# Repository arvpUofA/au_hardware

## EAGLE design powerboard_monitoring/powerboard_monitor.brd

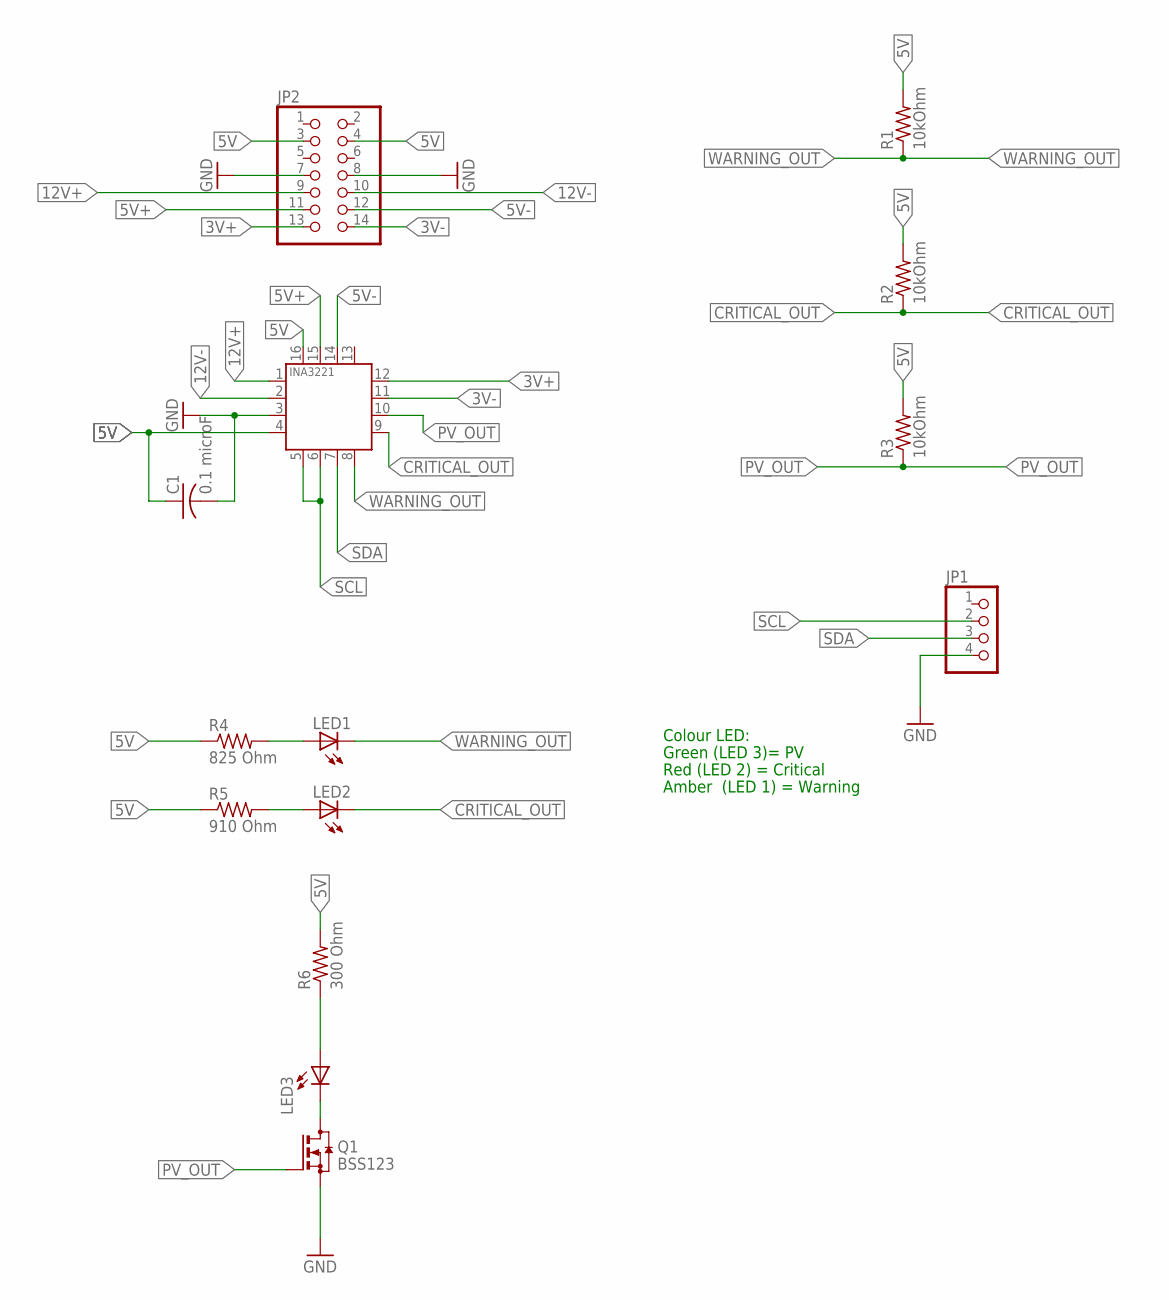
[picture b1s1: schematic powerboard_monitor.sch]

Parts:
C1: 0.1 microF; C1206
JP1: PINHD-1X4; 1X04
JP2: PINHD-2X7; 2X07
LED1, LED2, LED3: LEDSMT1206; 1206
Q1: BSS123; SOT23
R1, R2, R3: 10kOhm; R1206
R4: 825 Ohm; R1206
R5: 910 Ohm; R1206
R6: 300 Ohm; R1206
U1: INA3221.; HVQFN16_4X4

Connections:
3V+: JP2.13, U1.12 (IN+1)
3V-: JP2.14, U1.11 (IN-1)
5V: C1.1, JP2.3, JP2.4, R1.2, R2.2, R3.2, R4.1, R5.1, R6.2, U1.4 (VS), U1.16 (VPU)
5V+: JP2.11, U1.15 (IN+2)
5V-: JP2.12, U1.14 (IN-2)
12V+: JP2.9, U1.1 (IN-3)
12V-: JP2.10, U1.2 (IN+3)
CRITICAL_OUT: LED2.C, R2.1, U1.9 (CRITICAL)
GND: C1.2, JP1.4, JP2.7, JP2.8, Q1.2 (S), U1.3 (GND); also elsewhere on the board
unnamed: LED3.A, R6.1
unnamed: LED3.C, Q1.3 (D)
unnamed: LED1.A, R4.2
unnamed: LED2.A, R5.2
PV_OUT: Q1.1 (G), R3.1, U1.10 (PV)
SCL: JP1.2, U1.5 (A0), U1.6 (SCL); also elsewhere on the board
SDA: JP1.3, U1.7 (SDA); also elsewhere on the board
WARNING_OUT: LED1.C, R1.1, U1.8 (WARNING)

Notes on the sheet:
Colour LED:
Green (LED 3)= PV
Red (LED 2) = Critical
Amber (LED 1) = Warning

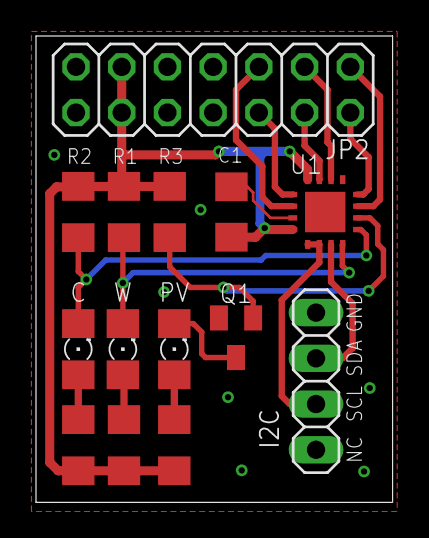
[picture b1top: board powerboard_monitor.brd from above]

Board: 2 copper layers, 19.8 x 25.9 mm, 16 parts (0 on the bottom side), 17 nets.

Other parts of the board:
I2C: 1X04
U$1: LETTER_P
U$2: DOCFIELD

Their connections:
GND: I2C.4; also elsewhere on the board
SCL: I2C.2; also elsewhere on the board
SDA: I2C.3; also elsewhere on the board

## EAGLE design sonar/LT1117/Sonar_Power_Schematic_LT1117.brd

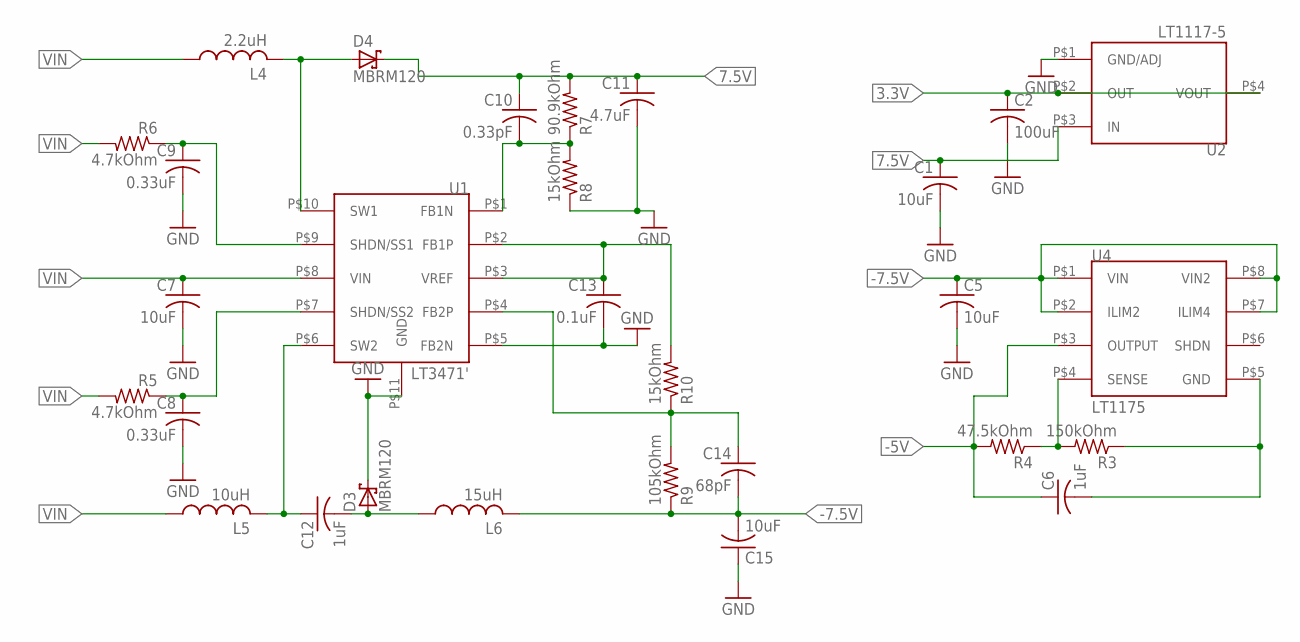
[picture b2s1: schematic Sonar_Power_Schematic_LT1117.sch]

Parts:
C1, C5, C7, C15: 10uF; C0603
C2: 100uF; C1210
C6, C12: 1uF; C0603
C8, C9: 0.33uF; C0603
C10: 0.33pF; C0603
C11: 4.7uF; C0603
C13: 0.1uF; C0603
C14: 68pF; C0603
D3, D4: MBRM120; DO-216AA
L4: 2.2uH; NS4.9X4.9
L5: 10uH; NS5X5
L6: 15uH; NS5X5
R3: 150kOhm; R0603
R4: 47.5kOhm; R0603
R5, R6: 4.7kOhm; R0603
R7: 90.9kOhm; R0603
R8, R10: 15kOhm; R0603
R9: 105kOhm; R0603
U1: LT3471'; 10-WFDFN
U2: LT1117-5; SOT233-3
U4: LT1175; 8-SOIC

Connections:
3.3V: C2.1, U2.P$2 (OUT), U2.P$4 (VOUT)
7.5V: C1.1, C10.1, C11.1, D4.P$1 (C), R7.2, U2.P$3 (IN)
-5V: C6.1, R4.2, U4.P$3 (OUTPUT)
-7.5V: C5.1, C14.2, C15.2, L6.P$2 (2), R9.1, U4.P$1 (VIN), U4.P$2 (ILIM2), U4.P$7 (ILIM4), U4.P$8 (VIN2)
GND: C1.2, C2.2, C5.2, C7.2, C8.2, C9.2, C11.2, C13.2, C15.1, D3.P$1 (C), R8.1, U1.P$5 (FB2N), U1.P$11 (GND), U2.P$1 (GND/ADJ)
unnamed: R3.2, R4.1, U4.P$4 (SENSE)
unnamed: C6.2, R3.1, U4.P$5 (GND)
unnamed: D4.P$2 (A), L4.P$2 (2), U1.P$10 (SW1)
unnamed: C10.2, R7.1, R8.2, U1.P$1 (FB1N)
unnamed: C12.1, L5.P$2 (2), U1.P$6 (SW2)
unnamed: C12.2, D3.P$2 (A), L6.P$1 (1)
unnamed: C14.1, R9.2, R10.1, U1.P$4 (FB2P)
SS1: C9.1, R6.1, U1.P$9 (SHDN/SS1)
SS2: C8.1, R5.1, U1.P$7 (SHDN/SS2)
VIN: C7.1, L4.P$1 (1), L5.P$1 (1), R5.2, R6.2, U1.P$8 (VIN)
VREF: C13.1, R10.2, U1.P$2 (FB1P), U1.P$3 (VREF)

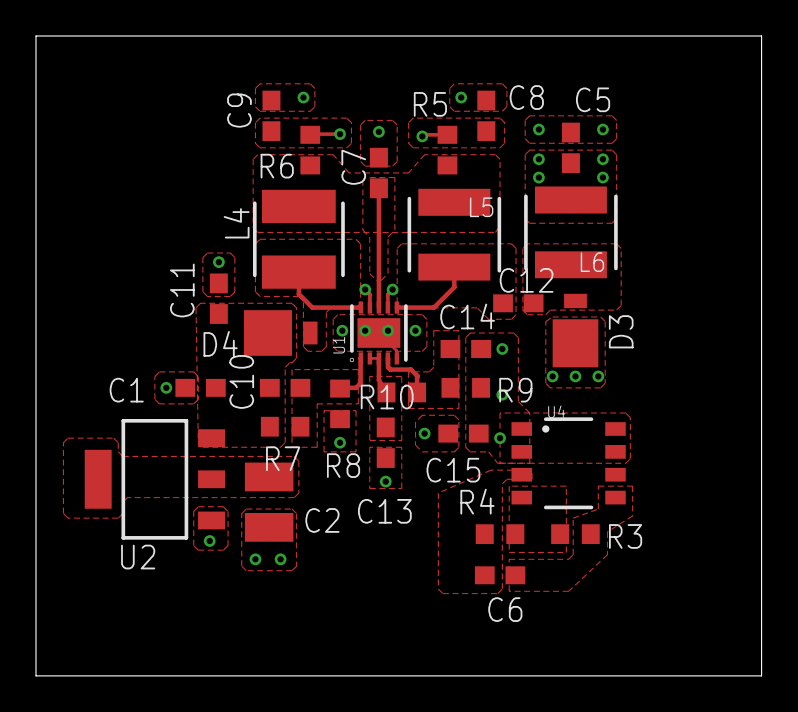
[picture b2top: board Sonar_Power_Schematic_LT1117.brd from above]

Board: 4 copper layers, 40.3 x 35.5 mm, 29 parts (0 on the bottom side), 16 nets.

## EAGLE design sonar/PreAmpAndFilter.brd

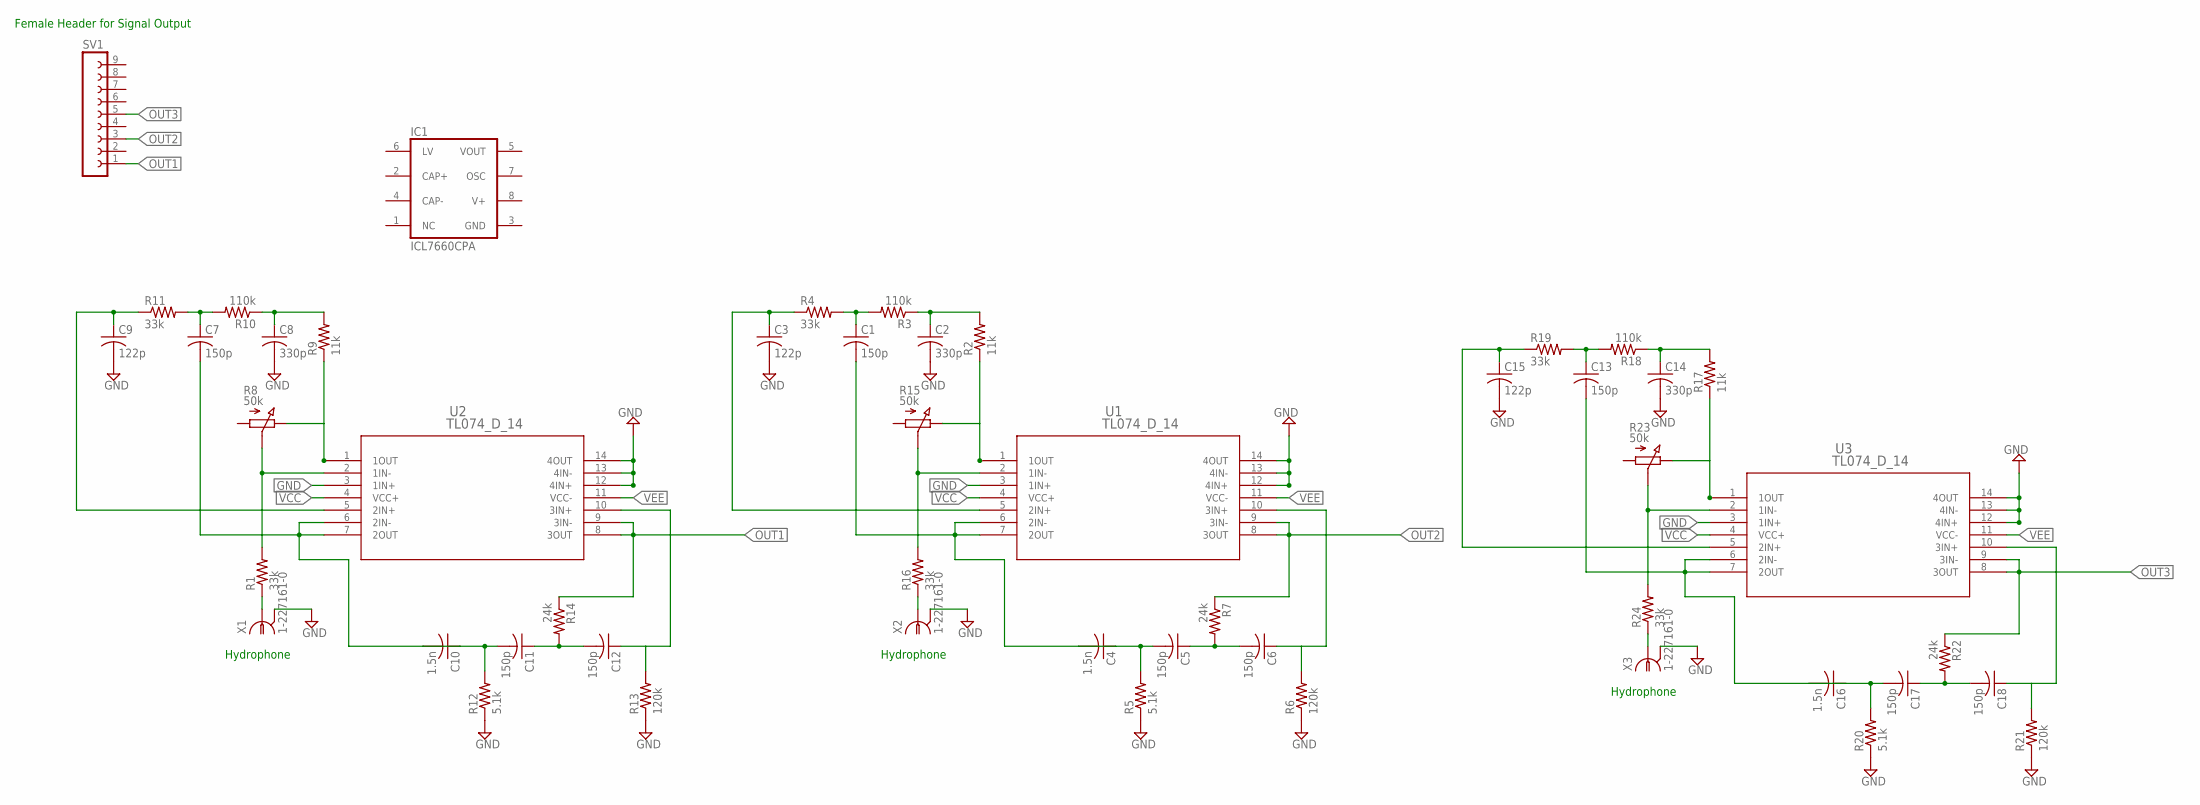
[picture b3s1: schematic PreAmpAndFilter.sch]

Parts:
C1, C5, C6, C7, C11, C12, C13, C17, C18: 150p; C025-024X044
C2, C8, C14: 330p; C025-024X044
C3, C9, C15: 122p; C025-024X044
C4, C10, C16: 1.5n; C025-024X044
IC1: ICL7660CPA; DIL08
R1, R4, R11, R16, R19, R24: 33k; 0204V
R2, R9, R17: 11k; 0204V
R3, R10, R18: 110k; 0204V
R5, R12, R20: 5.1k; 0204V
R6, R13, R21: 120k; 0204V
R7, R14, R22: 24k; 0204V
R8, R15, R23: 50k; PC25
SV1: FE09-1; FE09
U1, U2, U3: TL074_D_14; D14
X1, X2, X3: 1-227161-0; AMP_227161

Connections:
GND: C2.2, C3.2, C8.2, C9.2, C14.2, C15.2, IC1.3 (GND), R1.2, R5.1, R6.1, R8.S, R12.1, R13.1, R15.S, R16.2, R20.1, R21.1, R23.S, R24.2, U1.2 (1IN-), U1.3 (1IN+), U1.12 (4IN+), U1.13 (4IN-), U1.14 (4OUT), U2.2 (1IN-), U2.3 (1IN+), U2.12 (4IN+), U2.13 (4IN-), U2.14 (4OUT), U3.2 (1IN-), U3.3 (1IN+), U3.12 (4IN+), U3.13 (4IN-), U3.14 (4OUT), X1.2, X2.2, X3.2
unnamed: R1.1, X1.1
unnamed: R2.1, R15.E, U1.1 (1OUT)
unnamed: C2.1, R2.2, R3.1
unnamed: C1.1, R3.2, R4.2
unnamed: C1.2, C4.1, C4.2, C5.2, R5.2, U1.6 (2IN-), U1.7 (2OUT)
unnamed: C5.1, C6.2, R7.2
unnamed: R8.E, R9.1, U2.1 (1OUT)
unnamed: C8.1, R9.2, R10.1
unnamed: C7.1, R10.2, R11.2
unnamed: C7.2, C10.1, C10.2, C11.2, R12.2, U2.6 (2IN-), U2.7 (2OUT)
unnamed: C11.1, C12.2, R14.2
unnamed: R16.1, X2.1
unnamed: R17.1, R23.E, U3.1 (1OUT)
unnamed: C14.1, R17.2, R18.1
unnamed: C13.1, R18.2, R19.2
unnamed: C13.2, C16.1, C16.2, C17.2, R20.2, U3.6 (2IN-), U3.7 (2OUT)
unnamed: C17.1, C18.2, R22.2
unnamed: R24.1, X3.1
OUT1: R14.1, SV1.1, U2.8 (3OUT), U2.9 (3IN-)
OUT2: R7.1, SV1.3, U1.8 (3OUT), U1.9 (3IN-)
OUT3: R22.1, SV1.5, U3.8 (3OUT), U3.9 (3IN-)
V+: IC1.8 (V+)
VCC: U1.4 (VCC+), U2.4 (VCC+), U3.4 (VCC+)
VCC+: C9.1, R11.1, U2.5 (2IN+)
VCC+1: C3.1, R4.1, U1.5 (2IN+)
VCC+2: C15.1, R19.1, U3.5 (2IN+)
VCC-: C12.1, R13.2, U2.10 (3IN+)
VCC-1: C6.1, R6.2, U1.10 (3IN+)
VCC-2: C18.1, R21.2, U3.10 (3IN+)
VEE: U1.11 (VCC-), U2.11 (VCC-), U3.11 (VCC-)

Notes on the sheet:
Female Header for Signal Output
Hydrophone

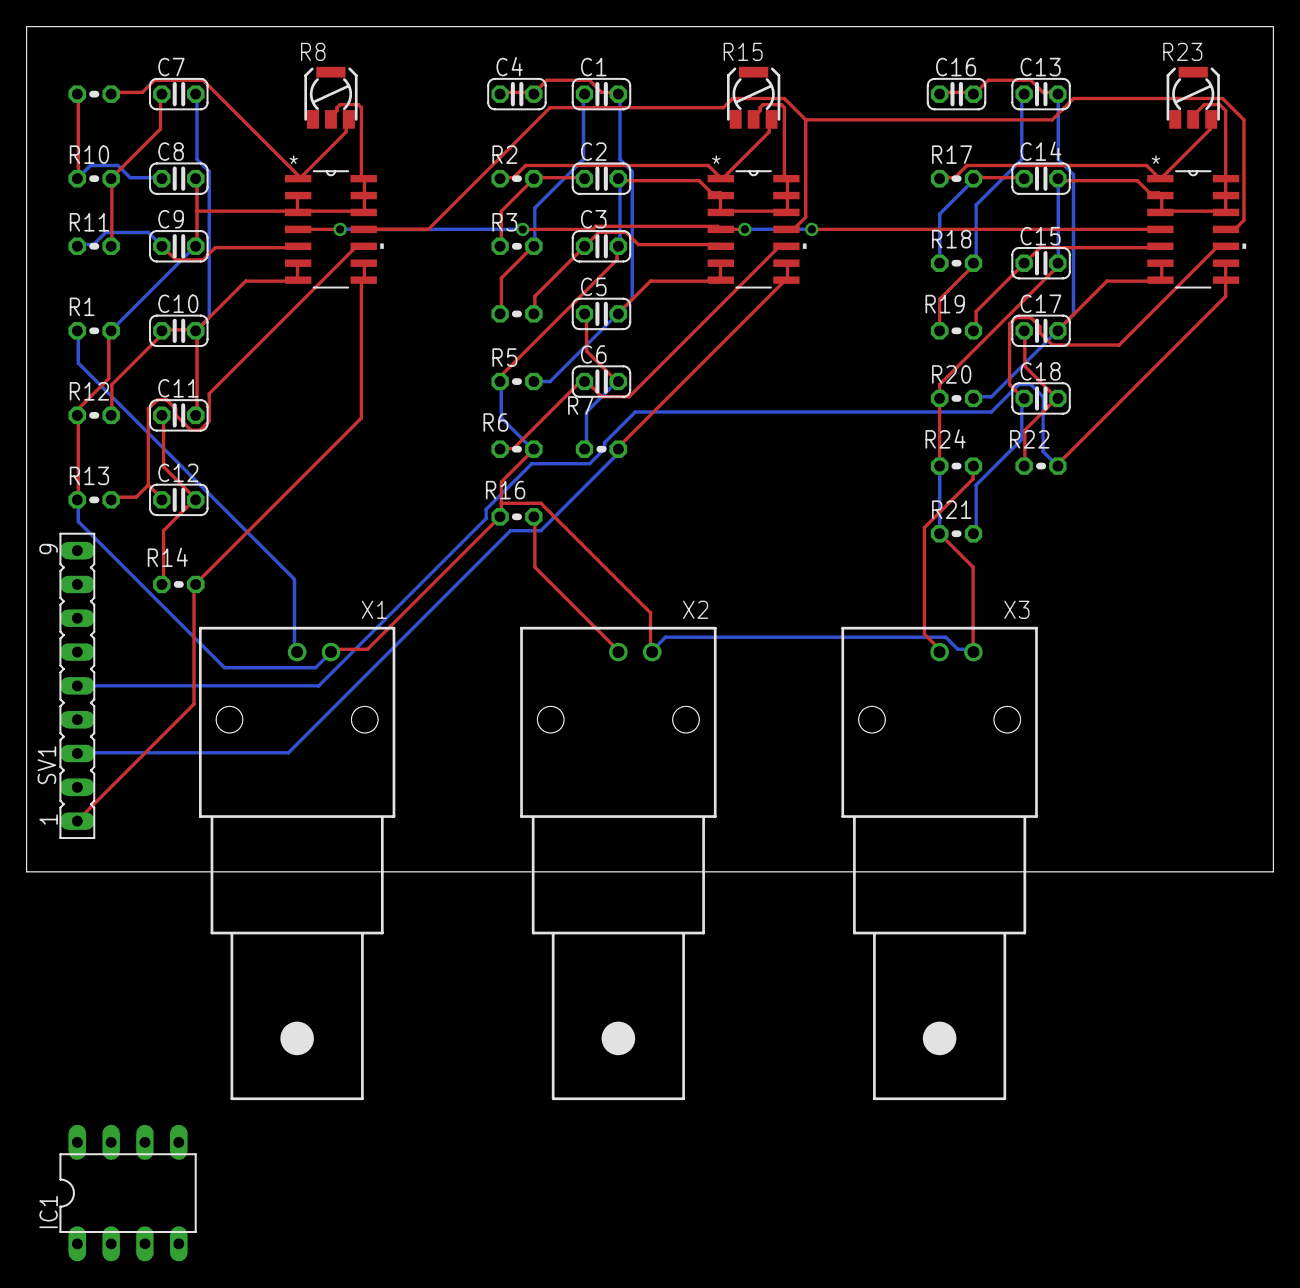
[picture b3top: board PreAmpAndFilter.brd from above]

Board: 2 copper layers, 93.7 x 63.5 mm, 50 parts (0 on the bottom side), 30 nets.

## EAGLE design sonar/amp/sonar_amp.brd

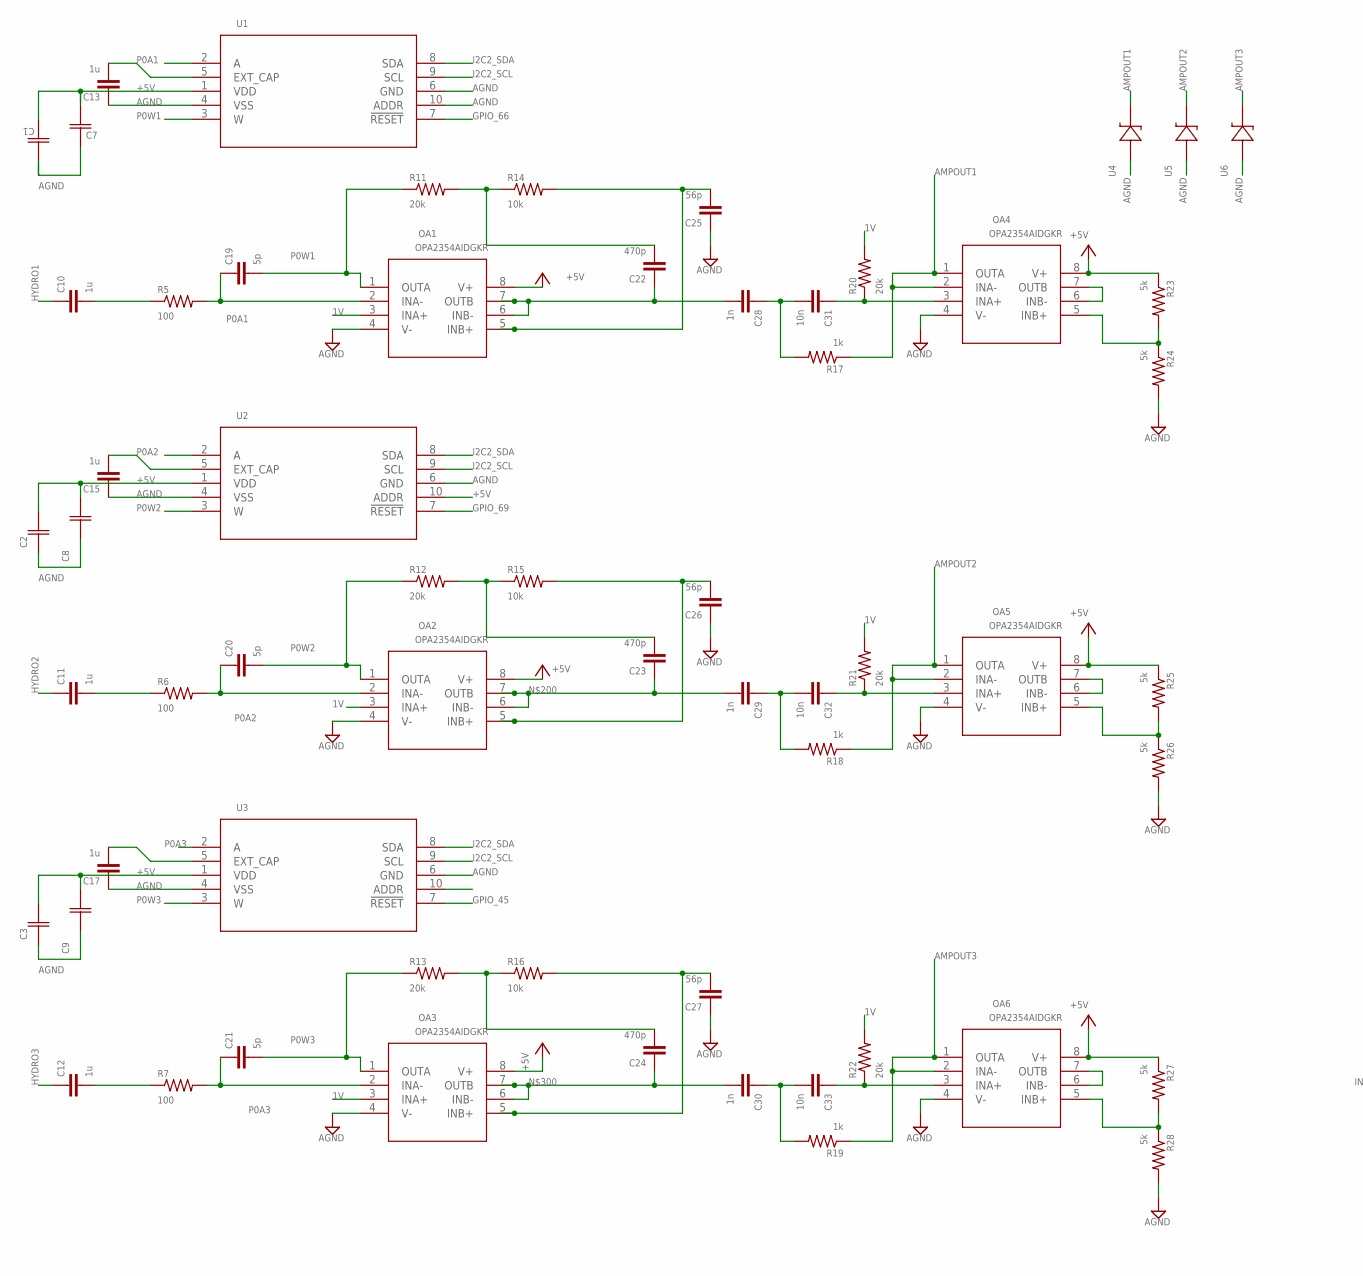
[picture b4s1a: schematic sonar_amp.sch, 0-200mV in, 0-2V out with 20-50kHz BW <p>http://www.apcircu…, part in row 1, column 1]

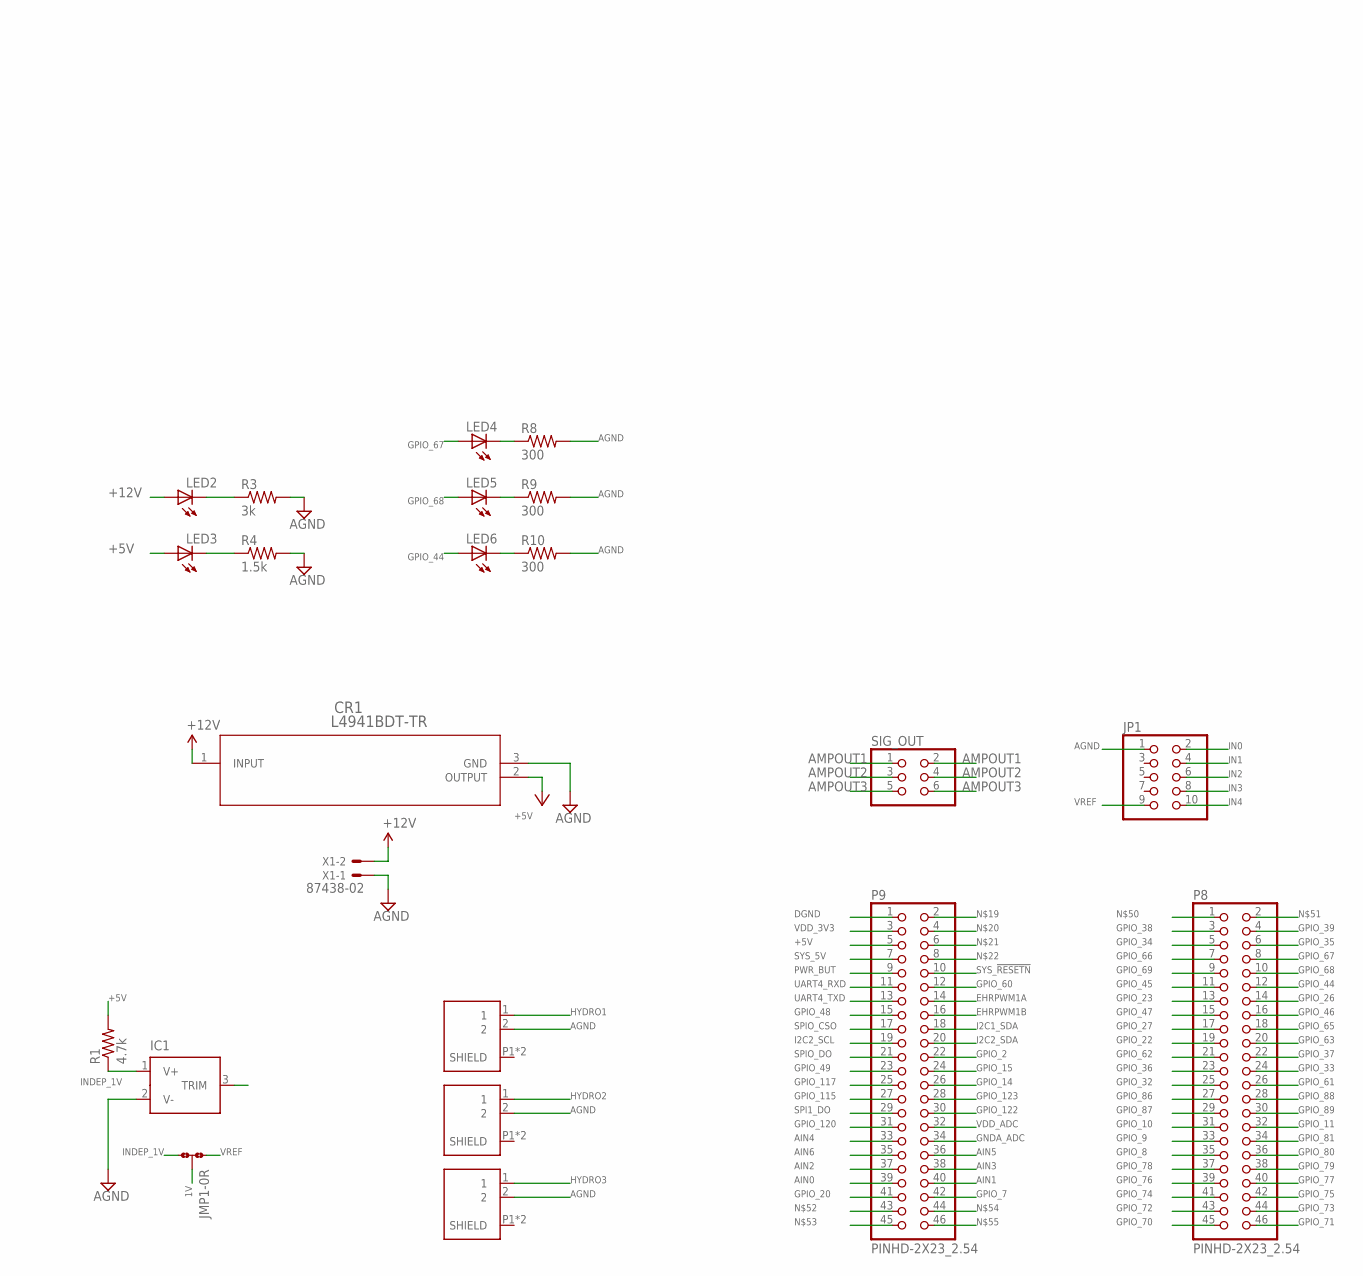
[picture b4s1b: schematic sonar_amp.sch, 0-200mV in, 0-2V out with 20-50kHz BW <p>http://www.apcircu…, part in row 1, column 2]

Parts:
C1, C2, C3: CC0805KRX7R7BB104; CC0805N
C7, C8, C9: CC0805ZKY5V6BB106; YAG_CC0805
C10, C11, C12, C13, C15, C17: 1u; 0805-CAP
C19, C20, C21: 5p; 0805-CAP
C22, C23, C24: 470p; 0805-CAP
C25, C26, C27: 56p; 0805-CAP
C28, C29, C30: 1n; 0805-CAP
C31, C32, C33: 10n; 0805-CAP
CR1: L4941BDT-TR; DPAK
IC1: ADR510; SOT23
J1, J2, J3: 1-1337543-0; CONN_1-1337543-0
JMP1: 0R-JUMPC; C0R-JMP
JP1: PINHD-2X5; 2X05
LED2, LED3, LED4, LED5, LED6: LEDSMT1206; 1206
OA1, OA2, OA3, OA4, OA5, OA6: OPA2354AIDGKR; DGK8
P8, P9: PINHD-2X23_2.54; 2X23
R1: 4.7k; 0805
R3: 3k; 0805
R4: 1.5k; 0805
R5, R6, R7: 100; 0805
R8, R9, R10: 300; 0805
R11, R12, R13, R20, R21, R22: 20k; 0805
R14, R15, R16: 10k; 0805
R17, R18, R19: 1k; 0805
R23, R24, R25, R26, R27, R28: 5k; 0805
SIG_OUT: PINHD-2X3; 2X03
U1, U2, U3: AD5272BRMZ-20RM_10-L; RM_10-L
U4, U5, U6: CZRF52C2CZRF-M; CZRF-M
X1: 87438-02

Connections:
1V: JMP1.2, OA1.3 (INA+), OA2.3 (INA+), OA3.3 (INA+), R20.2, R21.2, R22.2
+5V: C1.2 (22), C2.2 (22), C3.2 (22), C7.2 (22), C8.2 (22), C9.2 (22), CR1.2 (OUTPUT), LED3.A, OA1.8 (V+), OA2.8 (V+), OA3.8 (V+), OA4.8 (V+), OA5.8 (V+), OA6.8 (V+), P9.5, R1.2, R23.1, R25.1, R27.1, U1.1 (VDD), U2.1 (VDD), U2.10 (ADDR), U3.1 (VDD)
AIN0: P9.39
AIN1: P9.40
AIN2: P9.37
AIN3: P9.38
AIN4: P9.33
AIN5: P9.36
AIN6: P9.35
AMPOUT1: OA4.1 (OUTA), OA4.2 (INA-), R17.1, SIG_OUT.1, SIG_OUT.2, U4.1 (11)
AMPOUT2: OA5.1 (OUTA), OA5.2 (INA-), R18.1, SIG_OUT.3, SIG_OUT.4, U5.1 (11)
AMPOUT3: OA6.1 (OUTA), OA6.2 (INA-), R19.1, SIG_OUT.5, SIG_OUT.6, U6.1 (11)
DGND: P9.1
EHRPWM1A: P9.14
EHRPWM1B: P9.16
EXT_CAP: C13.2, U1.5 (EXT_CAP)
GNDA_ADC: P9.34
GPIO_2: P9.22
GPIO_7: P9.42
GPIO_8: P8.35
GPIO_9: P8.33
GPIO_10: P8.31
GPIO_11: P8.32
GPIO_14: P9.26
GPIO_15: P9.24
GPIO_20: P9.41
GPIO_22: P8.19
GPIO_23: P8.13
GPIO_26: P8.14
GPIO_27: P8.17
GPIO_32: P8.25
GPIO_33: P8.24
GPIO_34: P8.5
GPIO_35: P8.6
GPIO_36: P8.23
GPIO_37: P8.22
GPIO_38: P8.3
GPIO_39: P8.4
GPIO_44: LED6.A, P8.12
GPIO_45: P8.11, U3.7 (!RESET)
GPIO_46: P8.16
GPIO_47: P8.15
GPIO_48: P9.15
GPIO_49: P9.23
GPIO_60: P9.12
GPIO_61: P8.26
GPIO_62: P8.21
GPIO_63: P8.20
GPIO_65: P8.18
GPIO_66: P8.7, U1.7 (!RESET)
GPIO_67: LED4.A, P8.8
GPIO_68: LED5.A, P8.10
GPIO_69: P8.9, U2.7 (!RESET)
GPIO_70: P8.45
GPIO_71: P8.46
GPIO_72: P8.43
GPIO_73: P8.44
GPIO_74: P8.41
GPIO_75: P8.42
GPIO_76: P8.39
GPIO_77: P8.40
GPIO_78: P8.37
GPIO_79: P8.38
GPIO_80: P8.36
GPIO_81: P8.34
GPIO_86: P8.27
GPIO_87: P8.29
GPIO_88: P8.28
GPIO_89: P8.30
GPIO_115: P9.27
GPIO_117: P9.25
GPIO_120: P9.31
GPIO_122: P9.30
GPIO_123: P9.28
HYDRO1: C10.1, J1.1
HYDRO2: C11.1, J2.1
HYDRO3: C12.1, J3.1
I2C1_SDA: P9.18
I2C2_SCL: P9.19, U1.9 (SCL), U2.9 (SCL), U3.9 (SCL)
I2C2_SDA: P9.20, U1.8 (SDA), U2.8 (SDA), U3.8 (SDA)
IN0: JP1.2
IN1: JP1.4
IN2: JP1.6
IN3: JP1.8
IN4: JP1.10
INDEP_1V: IC1.1 (V+), JMP1.3, R1.1
unnamed: C23.2, R12.2, R15.1
unnamed: C22.2, R11.2, R14.1
unnamed: C29.1, C32.2, R18.2
unnamed: C32.1, OA5.3 (INA+), R21.1
unnamed: C28.1, C31.2, R17.2
unnamed: C31.1, OA4.3 (INA+), R20.1
unnamed: LED2.C, R3.1
unnamed: LED3.C, R4.1
unnamed: LED4.C, R8.1
unnamed: OA6.5 (INB+), R27.2, R28.1
unnamed: C24.2, R13.2, R16.1
unnamed: C30.1, C33.2, R19.2
unnamed: C33.1, OA6.3 (INA+), R22.1
unnamed: OA6.6 (INB-), OA6.7 (OUTB)
unnamed: OA4.5 (INB+), R23.2, R24.1
unnamed: LED5.C, R9.1
unnamed: LED6.C, R10.1
unnamed: C15.2, U2.5 (EXT_CAP)
unnamed: C17.2, U3.5 (EXT_CAP)
unnamed: OA4.6 (INB-), OA4.7 (OUTB)
unnamed: C22.1, C28.2, OA1.6 (INB-), OA1.7 (OUTB)
unnamed: OA5.6 (INB-), OA5.7 (OUTB)
unnamed: OA5.5 (INB+), R25.2, R26.1
unnamed: C26.2, OA2.5 (INB+), R15.2
unnamed: C25.2, OA1.5 (INB+), R14.2
unnamed: C23.1, C29.2, OA2.6 (INB-), OA2.7 (OUTB)
unnamed: C27.2, OA3.5 (INB+), R16.2
unnamed: C24.1, C30.2, OA3.6 (INB-), OA3.7 (OUTB)
P0A1: C19.1, OA1.2 (INA-), R5.2, U1.2 (A)
P0A2: C20.1, OA2.2 (INA-), R6.2, U2.2 (A)
P0A3: C21.1, OA3.2 (INA-), R7.2, U3.2 (A)
P0W1: C19.2, OA1.1 (OUTA), R11.1, U1.3 (W)
P0W2: C20.2, OA2.1 (OUTA), R12.1, U2.3 (W)
P0W3: C21.2, OA3.1 (OUTA), R13.1, U3.3 (W)
POB: C10.2, R5.1
POB1: C11.2, R6.1
POB2: C12.2, R7.1
PWR_BUT: P9.9
SPI1_DO: P9.29
SPIO_CSO: P9.17
SPIO_DO: P9.21
SYS_5V: P9.7
SYS_!RESETN: P9.10
UART4_RXD: P9.11
UART4_TXD: P9.13
VDD_3V3: P9.3
VDD_ADC: P9.32
VREF: JMP1.1, JP1.9

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
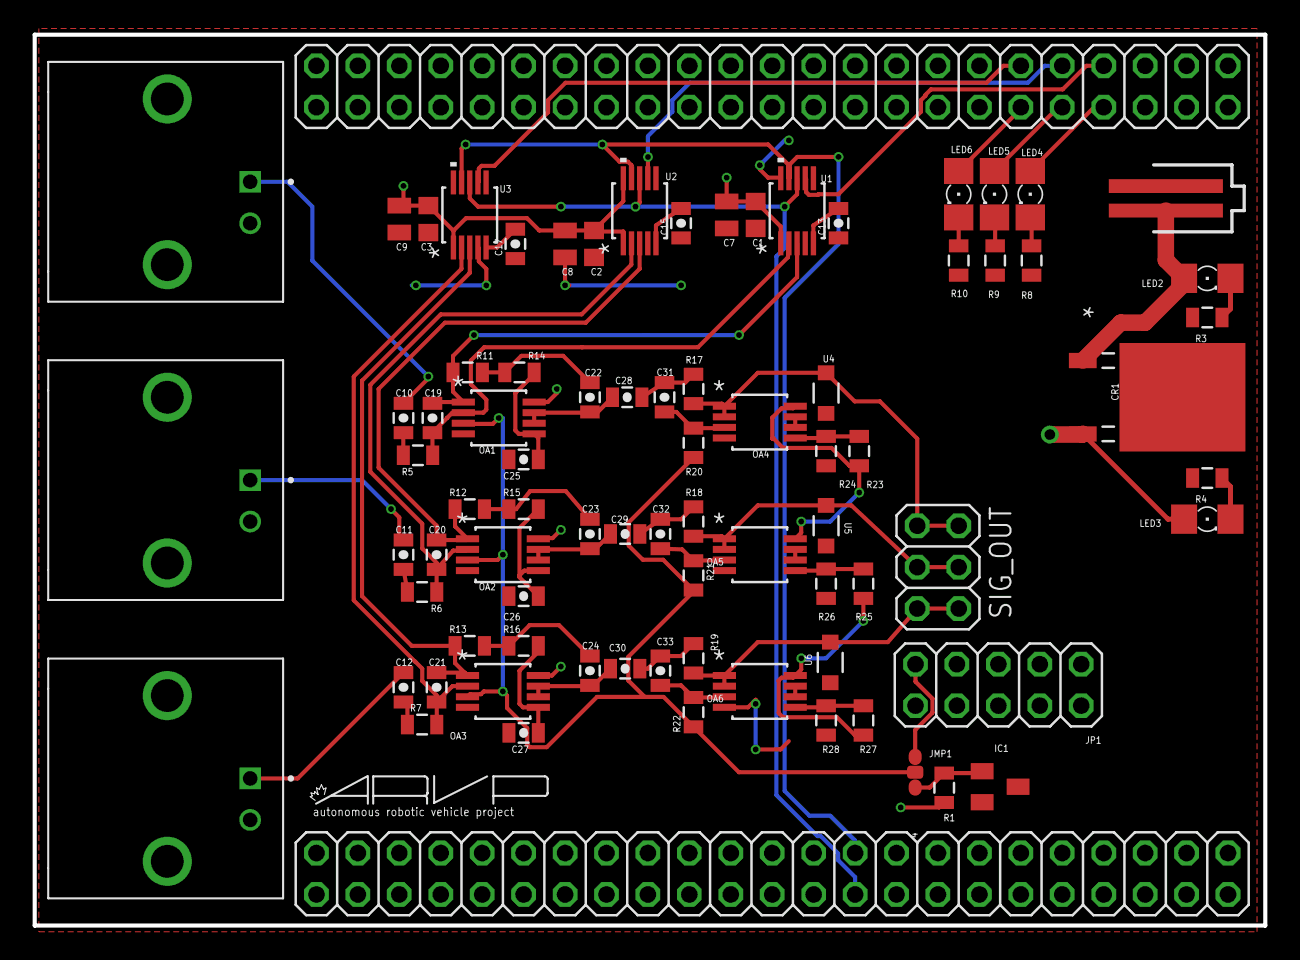
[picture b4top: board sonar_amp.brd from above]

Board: 2 copper layers, 75.4 x 54.6 mm, 83 parts (0 on the bottom side), 58 nets.

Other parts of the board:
U$1: ARVP

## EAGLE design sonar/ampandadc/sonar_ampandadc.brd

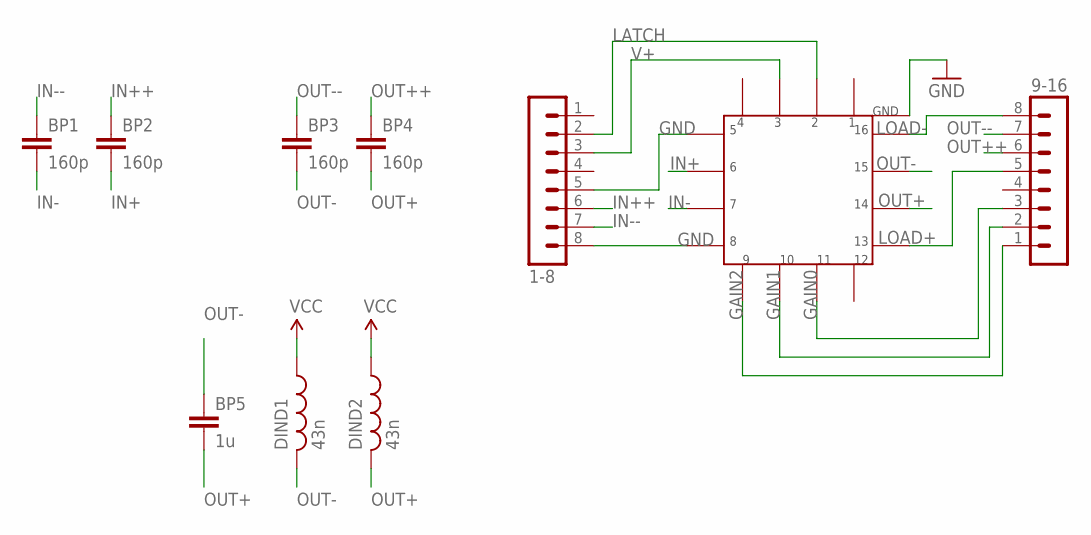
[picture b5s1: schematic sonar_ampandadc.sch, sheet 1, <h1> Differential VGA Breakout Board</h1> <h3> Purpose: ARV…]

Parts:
1-8, 9-16: MA08-1
BP1, BP2, BP3, BP4: 160p; 0603-CAP
BP5: 1u; 0603-CAP
DIND1, DIND2: 43n; 0402-RES
U$1: LMH6514; WQFN4X4

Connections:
GAIN0: 9-16.3, U$1.P$11
GAIN1: 9-16.2, U$1.P$10
GAIN2: 9-16.1, U$1.P$9
GND: 1-8.5, 1-8.8, U$1.GND, U$1.P$5, U$1.P$8; also elsewhere on the board
IN+: BP2.2, U$1.P$6
IN++: 1-8.6, BP2.1
IN-: BP1.2, U$1.P$7
IN--: 1-8.7, BP1.1
LATCH: 1-8.2, U$1.P$2
LOAD+: 9-16.5, U$1.P$13; also elsewhere on the board
LOAD-: 9-16.8, U$1.P$16; also elsewhere on the board
OUT+: BP4.2, BP5.2, DIND2.2, U$1.P$14
OUT++: 9-16.6, BP4.1; also elsewhere on the board
OUT-: BP3.2, BP5.1, DIND1.2, U$1.P$15
OUT--: 9-16.7, BP3.1; also elsewhere on the board
V+: 1-8.3, DIND1.1, DIND2.1, U$1.P$3; also elsewhere on the board

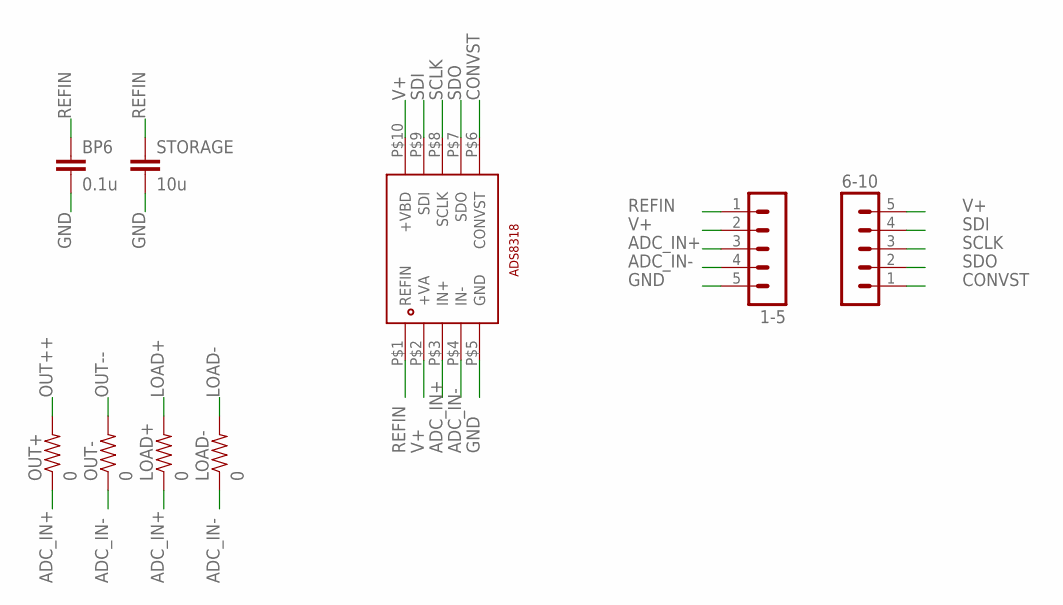
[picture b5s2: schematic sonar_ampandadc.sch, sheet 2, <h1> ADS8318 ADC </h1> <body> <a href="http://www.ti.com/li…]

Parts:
1-5, 6-10: MA05-1
BP6: 0.1u; 0603-CAP
LOAD+: 0; 0603-RES
LOAD-: 0; 0603-RES
OUT+: 0; 0603-RES
OUT-: 0; 0603-RES
STORAGE: 10u; 0603-CAP
U$2: ADS8318; 10-VSSOP

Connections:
ADC_IN+: 1-5.3, LOAD+.1, OUT+.1, U$2.P$3 (IN+)
ADC_IN-: 1-5.4, LOAD-.1, OUT-.1, U$2.P$4 (IN-)
CONVST: 6-10.1, U$2.P$6 (CONVST)
GND: 1-5.5, BP6.2, STORAGE.2, U$2.P$5 (GND); also elsewhere on the board
LOAD+: LOAD+.2; also elsewhere on the board
LOAD-: LOAD-.2; also elsewhere on the board
OUT++: OUT+.2; also elsewhere on the board
OUT--: OUT-.2; also elsewhere on the board
REFIN: 1-5.1, BP6.1, STORAGE.1, U$2.P$1 (REFIN)
SCLK: 6-10.3, U$2.P$8 (SCLK)
SDI: 6-10.4, U$2.P$9 (SDI)
SDO: 6-10.2, U$2.P$7 (SDO)
V+: 1-5.2, 6-10.5, U$2.P$2 (+VA), U$2.P$10 (+VBD); also elsewhere on the board

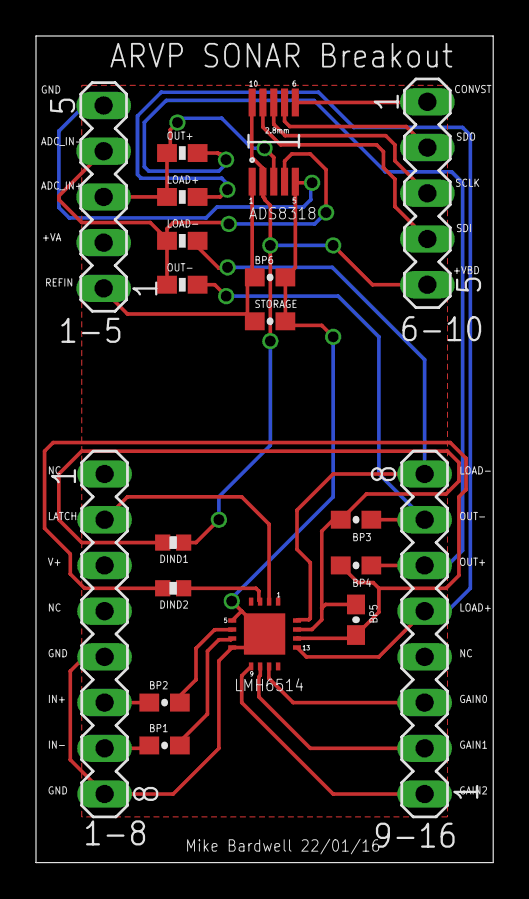
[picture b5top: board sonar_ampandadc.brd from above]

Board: 2 copper layers, 25.4 x 45.9 mm, 19 parts (0 on the bottom side), 23 nets.

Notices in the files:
parts and their libraries:
SparkFun-Capacitors: Licensing: Creative Commons ShareAlike 4.0 International - https://creativecommons.org/licenses/by-sa/4.0
